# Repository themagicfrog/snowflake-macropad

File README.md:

# Snowpad

This is a 3x3 macropad themed snow for Hack Club's Blueprint/Hackpad/Prototype. I like keyboards a lot and also it's winter which is why I chose to
make it winter-themed with the snowflake silkscreen, and the blue and white coloring on the 3D case. It also has a rotary encoder for things like adjusting volume. This was fun to make!

# BOM
- 9x SW_Cherry_MX_1.00u_PCB Switches
- 1x XIAO-RP2040-DIP 
- 9x D_T-1_P5.08mm_Horizontal Diodes
- 1x RotaryEncoder_Alps_EC11E-Switch_Vertical_H20mm

## Full Macropad!!

## PCB Render

## PCB in Kicad

## Schematic

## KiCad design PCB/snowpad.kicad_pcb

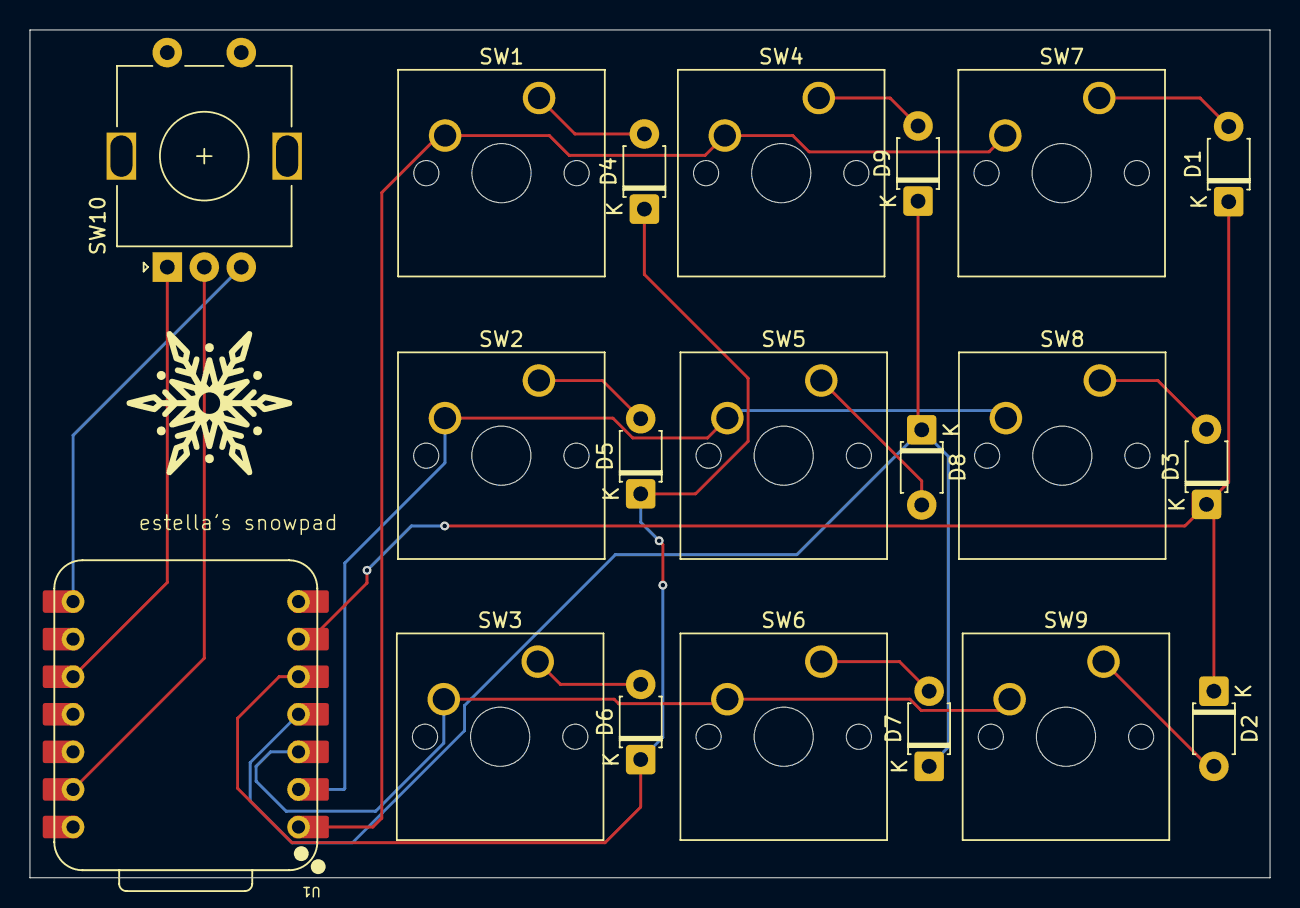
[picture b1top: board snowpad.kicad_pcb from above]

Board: 2 copper layers, 83.8 x 57.3 mm, 20 parts (0 on the bottom side), 18 nets.

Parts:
D1, D2, D3, D4, D5, D6, D7, D8, D9: D; D_T-1_P5.08mm_Horizontal
SW1, SW2, SW3, SW4, SW5, SW6, SW7, SW8, SW9: SW_Push; SW_Cherry_MX_1.00u_PCB
SW10: RotaryEncoder; RotaryEncoder_Alps_EC11E-Switch_Vertical_H20mm
U1: XIAO-RP2040-DIP

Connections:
GND: SW10.C, U1.13 (GND)
unnamed: D1.2 (A), SW7.1
unnamed: D2.2 (A), SW9.1
unnamed: D3.2 (A), SW8.1
unnamed: D4.2 (A), SW1.1
unnamed: D5.2 (A), SW2.1
unnamed: D6.2 (A), SW3.1
unnamed: D7.2 (A), SW6.1
unnamed: D8.2 (A), SW5.1
unnamed: D9.2 (A), SW4.1
unnamed: SW10.B, U1.8 (GPIO1/RX)
unnamed: SW10.A, U1.10 (GPIO4/MISO)
col1: SW1.2, SW4.2, SW7.2, U1.1 (GPIO26/ADC0/A0)
col2: SW2.2, SW5.2, SW8.2, U1.2 (GPIO27/ADC1/A1)
col3: SW3.2, SW6.2, SW9.2, U1.3 (GPIO28/ADC2/A2)
row0: D7.1 (K), D8.1 (K), D9.1 (K), U1.4 (GPIO29/ADC3/A3)
row1: D4.1 (K), D5.1 (K), D6.1 (K), U1.5 (GPIO6/SDA)
row2: D1.1 (K), D2.1 (K), D3.1 (K), U1.6 (GPIO7/SCL)

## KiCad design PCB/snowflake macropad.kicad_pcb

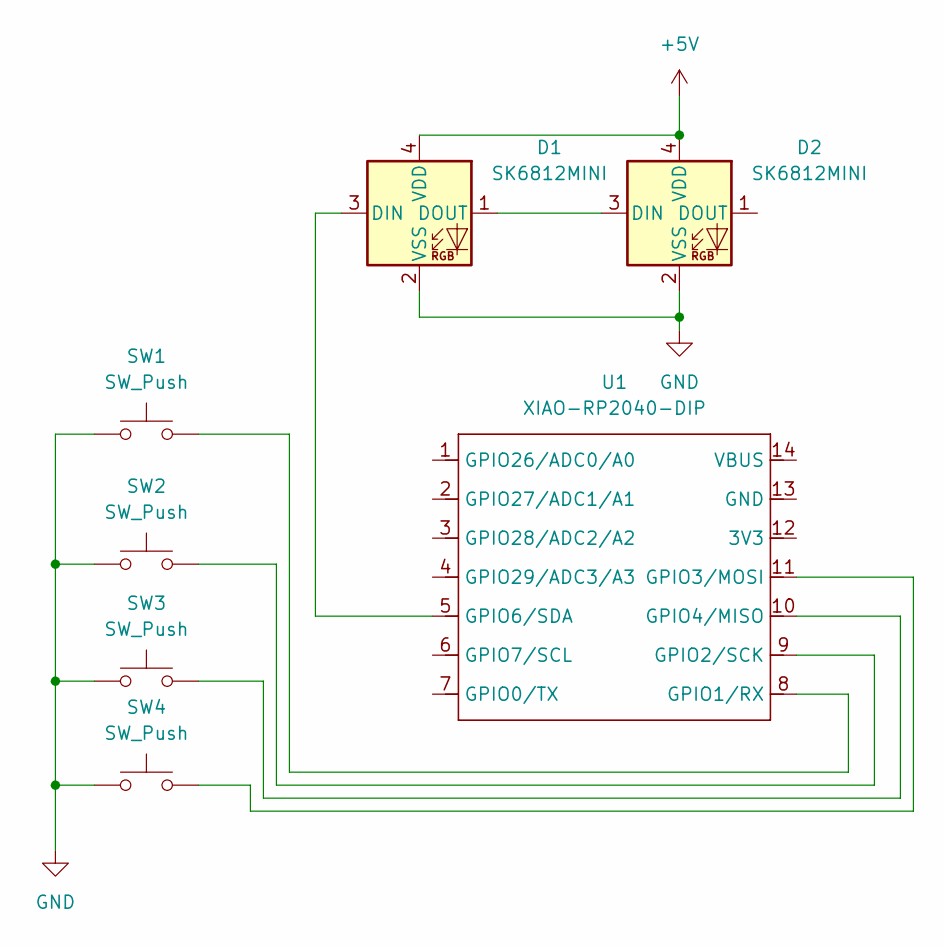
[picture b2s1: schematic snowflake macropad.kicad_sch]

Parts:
D1, D2: SK6812MINI; LED_SK6812MINI_PLCC4_3.5x3.5mm_P1.75mm
SW1, SW2, SW3, SW4: SW_Push; SW_Cherry_MX_1.00u_PCB
U1: XIAO-RP2040-DIP

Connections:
+5V: D1.4 (VDD), D2.4 (VDD)
GND: D1.2 (VSS), D2.2 (VSS), SW1.1, SW2.1, SW3.1, SW4.1
unnamed: D1.3 (DIN), U1.5 (GPIO6/SDA)
unnamed: D1.1 (DOUT), D2.3 (DIN)
unnamed: SW1.2, U1.8 (GPIO1/RX)
unnamed: SW2.2, U1.9 (GPIO2/SCK)
unnamed: SW4.2, U1.11 (GPIO3/MOSI)
unnamed: SW3.2, U1.10 (GPIO4/MISO)

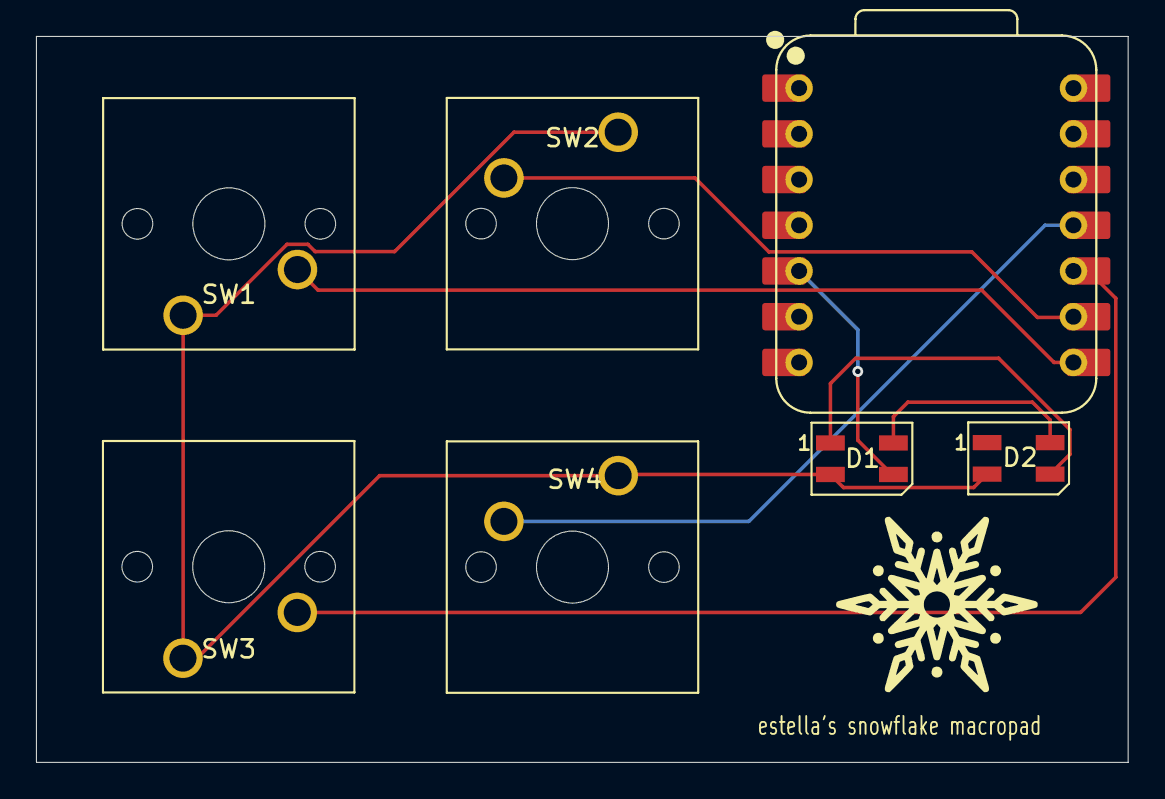
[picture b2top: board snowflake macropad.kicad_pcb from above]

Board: 2 copper layers, 60.7 x 40.3 mm, 7 parts (0 on the bottom side), 8 nets.

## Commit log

2025-11-29 init
2025-11-29 new init
